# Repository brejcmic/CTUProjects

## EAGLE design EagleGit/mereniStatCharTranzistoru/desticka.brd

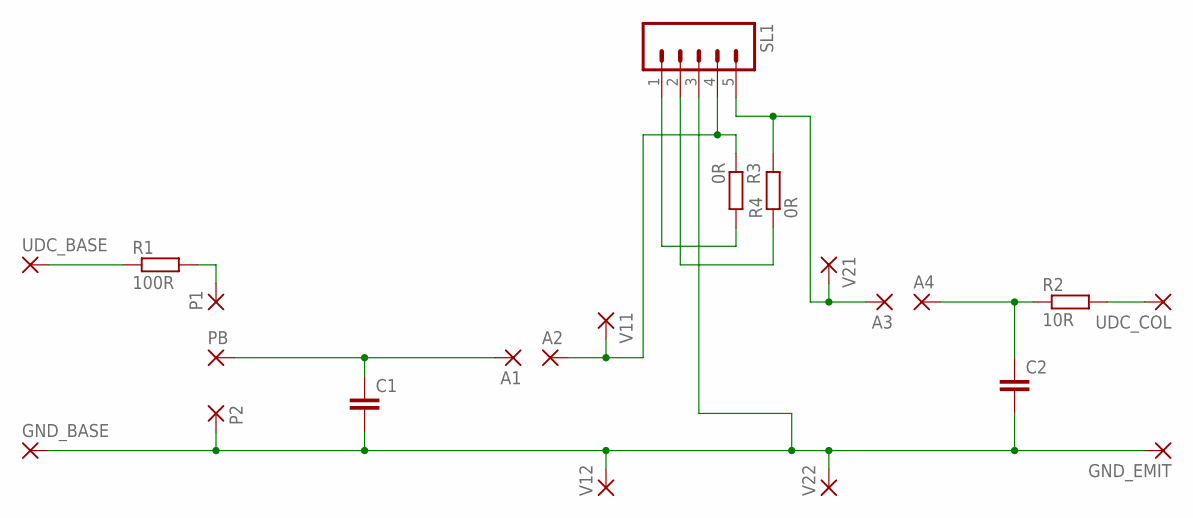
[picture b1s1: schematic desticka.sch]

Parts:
A1, A2, A3, A4: 3,17/1,3
C1, C2: C-EU050-055X075; C050-055X075
GND_BASE: 3,17/1,3
GND_EMIT: 3,17/1,3
P1, P2: 2,54/1,0
PB: 2,54/1,0
R1: 100R; P0613/15
R2: 10R; P0613/15
R3, R4: 0R; 0207/7
SL1: M05; 05P
UDC_BASE: 3,17/1,3
UDC_COL: 3,17/1,3
V11, V12, V21, V22: 3,17/1,3

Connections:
unnamed: A1.1, C1.1, PB.1
unnamed: R3.2, SL1.1
unnamed: R2.2, UDC_COL.1
unnamed: R1.1, UDC_BASE.1
unnamed: P1.1, R1.2
unnamed: R4.1, SL1.2
unnamed: A4.1, C2.1, R2.1
unnamed: C1.2, C2.2, GND_BASE.1, GND_EMIT.1, P2.1, SL1.3, V12.1, V22.1
unnamed: A3.1, R4.2, SL1.5, V21.1
unnamed: A2.1, R3.1, SL1.4, V11.1

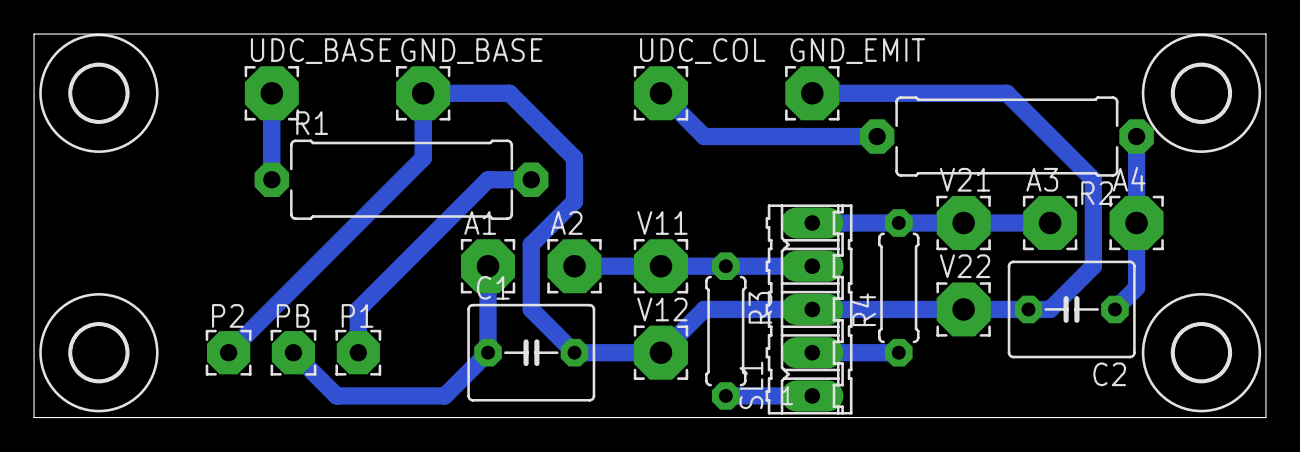
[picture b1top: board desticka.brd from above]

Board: 2 copper layers, 72.4 x 22.5 mm, 26 parts (0 on the bottom side), 10 nets.

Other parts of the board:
U$1, U$2, U$3, U$4: 3,2

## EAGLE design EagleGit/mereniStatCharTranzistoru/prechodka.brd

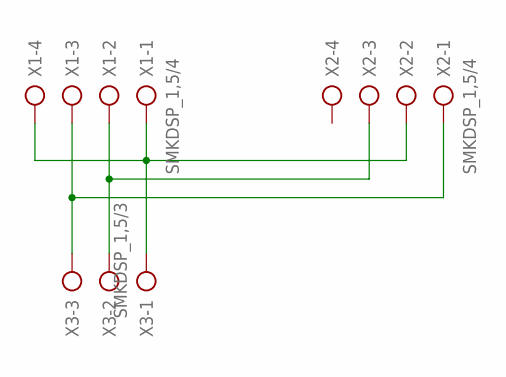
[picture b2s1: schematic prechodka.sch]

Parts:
X1, X2: SMKDSP_1,5/4
X3: SMKDSP_1,5/3

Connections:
BASE: X1.1, X1.4, X2.2, X3.1
COLECTOR: X1.2, X2.3, X3.2
EMITOR: X1.3, X2.1, X3.3

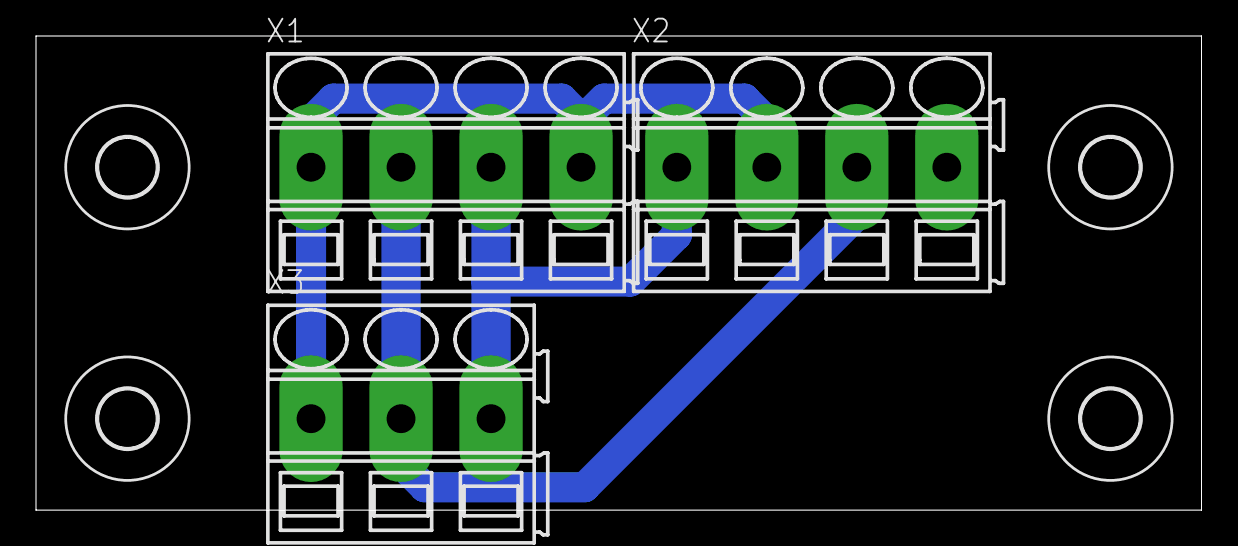
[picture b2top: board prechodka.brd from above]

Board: 2 copper layers, 64.8 x 26.3 mm, 7 parts (0 on the bottom side), 3 nets.

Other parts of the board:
U$1, U$2, U$3, U$4: 3,2

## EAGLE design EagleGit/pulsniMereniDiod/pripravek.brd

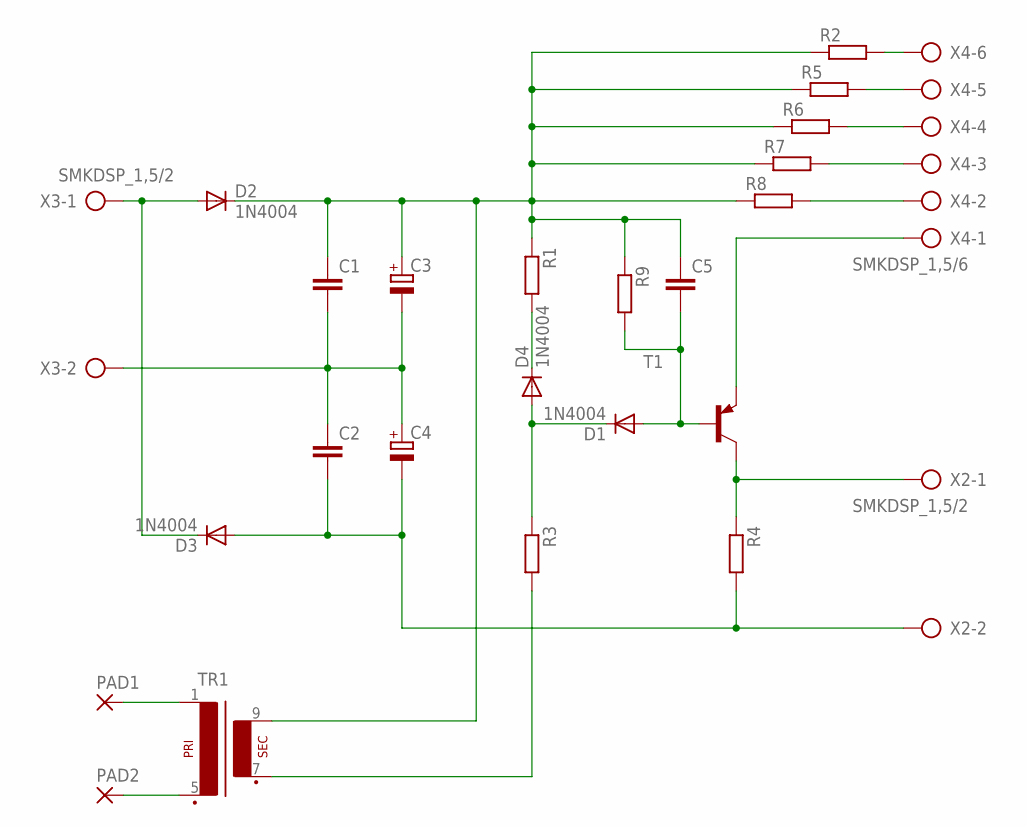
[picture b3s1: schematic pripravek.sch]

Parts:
C1, C2, C5: C-EU050-035X075; C050-035X075
C3, C4: CPOL-EUE5-8.5; E5-8,5
D1, D2, D3, D4: 1N4004; DO41-10
PAD1, PAD2: 3,81/1,3
R1, R3, R4, R9: R-EU_0207/12; 0207/12
R2, R5, R6, R7, R8: R-EU_0411/15; 0411/15
T1: -PNP-TO220V; TO220V
TR1: EI30-1
X2, X3: SMKDSP_1,5/2
X4: SMKDSP_1,5/6

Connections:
BASE: C5.2, D1.A, R9.2, T1.1 (B)
COLECTOR: R4.1, T1.2 (C), X2.1
EMITER: T1.3 (E), X4.1
unnamed: PAD1.1, TR1.1
unnamed: PAD2.1, TR1.5 (P2)
unnamed: R2.2, X4.6
unnamed: D1.C, D4.A, R3.1
unnamed: C1.2, C2.1, C3.-, C4.+, X3.2
unnamed: D4.C, R1.2
unnamed: D2.A, D3.C, X3.1
unnamed: C2.2, C4.-, D3.A, R4.2, X2.2
unnamed: R3.2, TR1.7 (S3)
unnamed: R5.2, X4.5
unnamed: C1.1, C3.+, C5.1, D2.C, R1.1, R2.1, R5.1, R6.1, R7.1, R8.1, R9.1, TR1.9 (S4)
unnamed: R6.2, X4.4
unnamed: R7.2, X4.3
unnamed: R8.2, X4.2

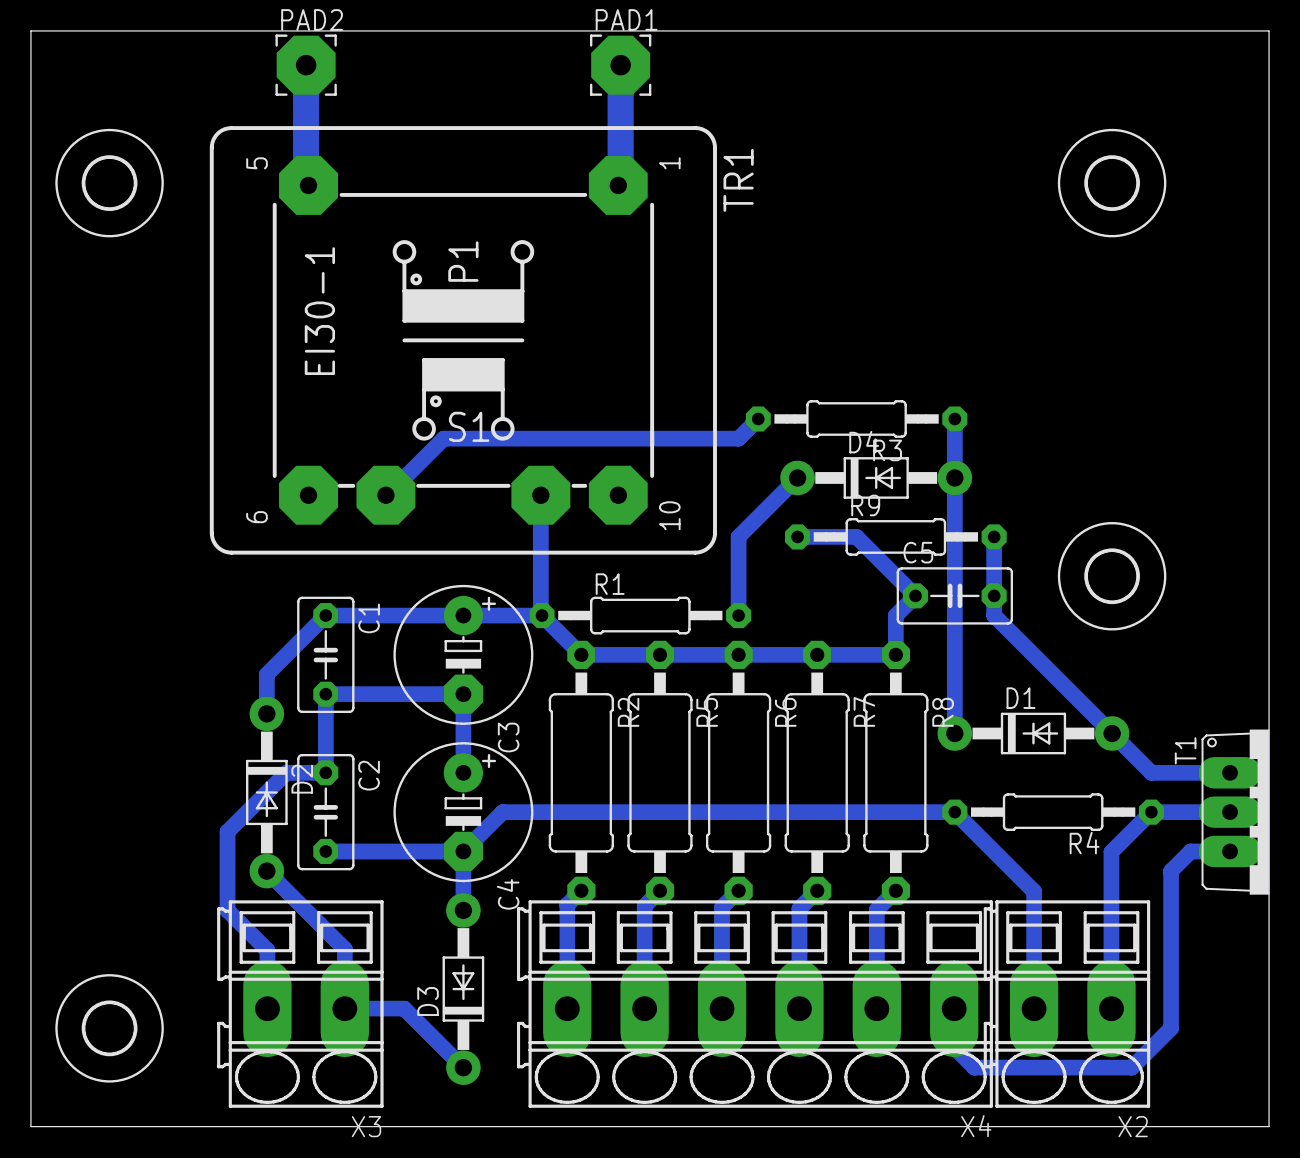
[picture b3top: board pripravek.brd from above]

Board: 2 copper layers, 80.0 x 70.8 mm, 29 parts (0 on the bottom side), 17 nets.

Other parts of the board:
U$1, U$2, U$3, U$4: 3,2

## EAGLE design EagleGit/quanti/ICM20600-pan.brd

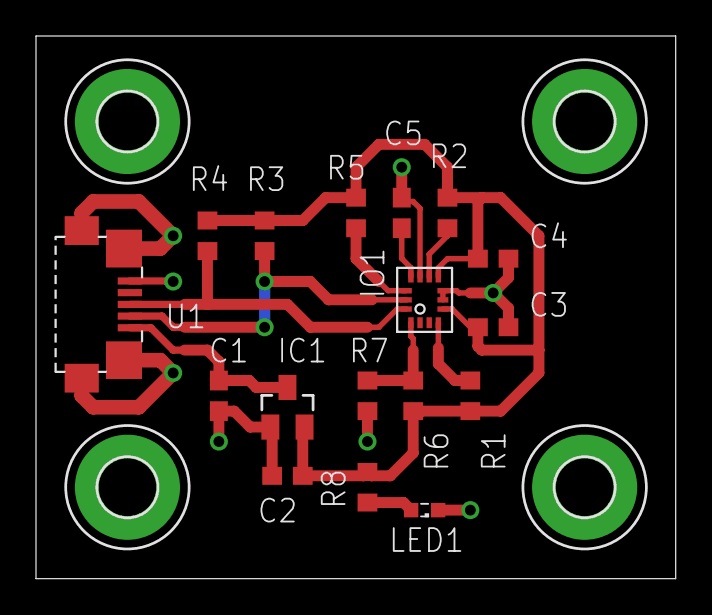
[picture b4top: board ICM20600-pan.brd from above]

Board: 2 copper layers, 35.5 x 30.1 mm, 21 parts (0 on the bottom side), 11 nets.

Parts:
C1, C2: 2u2; C0603
C3, C4, C5: 100n; C0603
H1, H2, H3, H4: MOUNT-PAD-ROUND3.2; 3,2-PAD
IC1: MCP1703CB; SOT23
IO1: LGA14
LED1: SML0603
R1, R2, R3, R4, R5, R6: 10k; R0603
R7: 0R; R0603
R8: 220R; R0603
U1: MICRO-USB-SHIELD-ZX62R-B-5P; ZX62R-B-5P

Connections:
+3V3: C2.1, C3.1, C4.1, IC1.2, IO1.P5, IO1.P8, R1.2, R2.2, R3.2, R4.2, R5.2, R6.2, R8.2
+5V: C1.1, IC1.3, U1.1
GND: C1.2, C2.2, C3.2, C4.2, C5.2, H1.B3,2, H2.B3,2, H3.B3,2, H4.B3,2, IC1.1, IO1.P6, IO1.P7, IO1.P10, LED1.C, R7.1, U1.5, U1.M1, U1.M2, U1.M3, U1.M4
unnamed: IO1.P9, R2.1
unnamed: IO1.P4, R1.1
unnamed: C5.1, IO1.P11
unnamed: IO1.P13, R3.1, U1.2
unnamed: IO1.P14, R4.1, U1.3
unnamed: IO1.P12, R5.1
unnamed: IO1.P1, R6.1, R7.2
unnamed: LED1.A, R8.1

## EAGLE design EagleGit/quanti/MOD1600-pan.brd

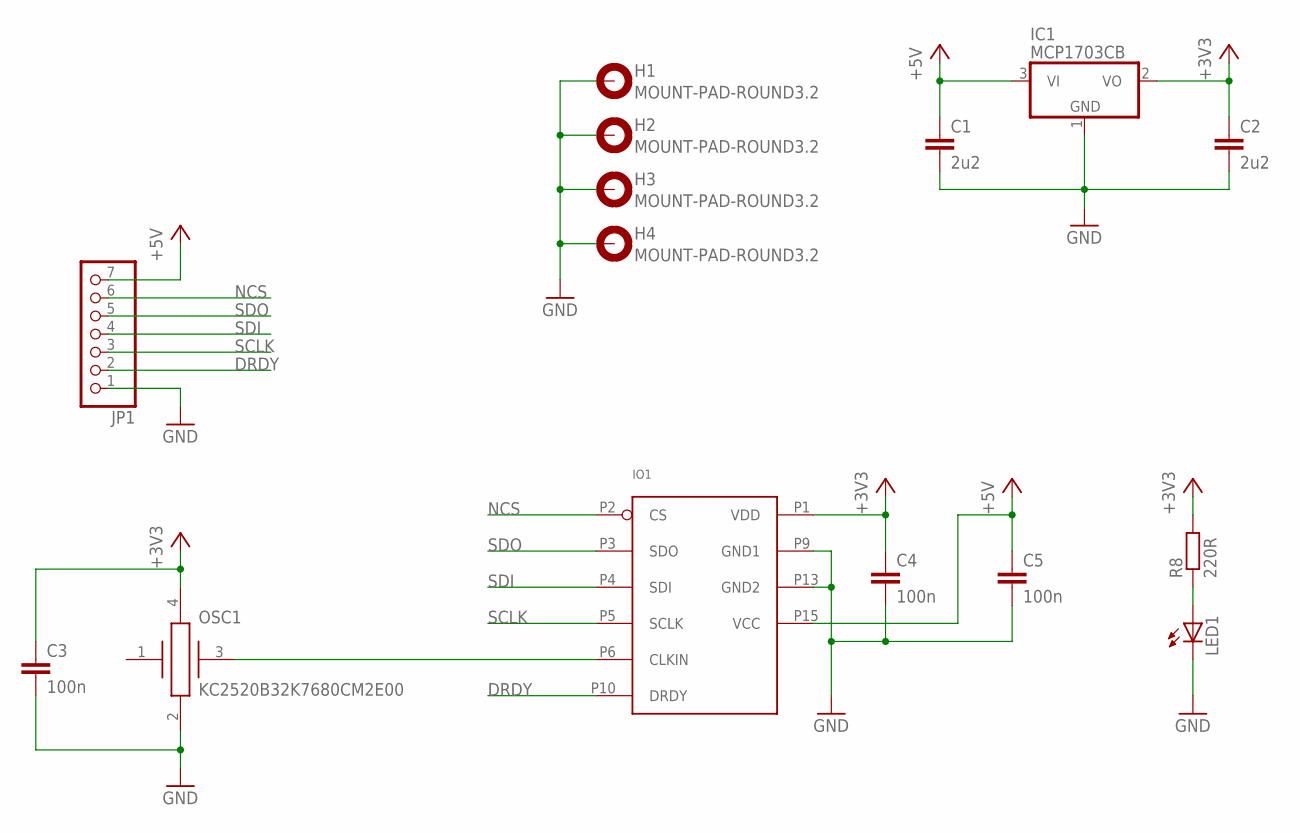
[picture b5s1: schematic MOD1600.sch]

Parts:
C1, C2: 2u2; C0603
C3, C4, C5: 100n; C0603
H1, H2, H3, H4: MOUNT-PAD-ROUND3.2; 3,2-PAD
IC1: MCP1703CB; SOT23
IO1: MOD1600; LGA_MOD1600
JP1: PINHD-1X7/90; 1X07/90
LED1: LEDSML0603; SML0603
OSC1: KC2520B32K7680CM2E00; SMD_OSC
R8: 220R; R0603

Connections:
+3V3: C2.1, C3.1, C4.1, IC1.2 (VO), IO1.P1 (VDD), OSC1.4 (VDD), R8.2
+5V: C1.1, C5.1, IC1.3 (VI), IO1.P15 (VCC), JP1.7
CLKIN: IO1.P6 (CLKIN), OSC1.3 (OUT)
DRDY: IO1.P10 (DRDY), JP1.2
GND: C1.2, C2.2, C3.2, C4.2, C5.2, H1.B3,2, H2.B3,2, H3.B3,2, H4.B3,2, IC1.1 (GND), IO1.P9 (GND1), IO1.P13 (GND2), JP1.1, LED1.C, OSC1.2 (GND)
unnamed: LED1.A, R8.1
NCS: IO1.P2 (CS), JP1.6
SCLK: IO1.P5 (SCLK), JP1.3
SDI: IO1.P4 (SDI), JP1.4
SDO: IO1.P3 (SDO), JP1.5

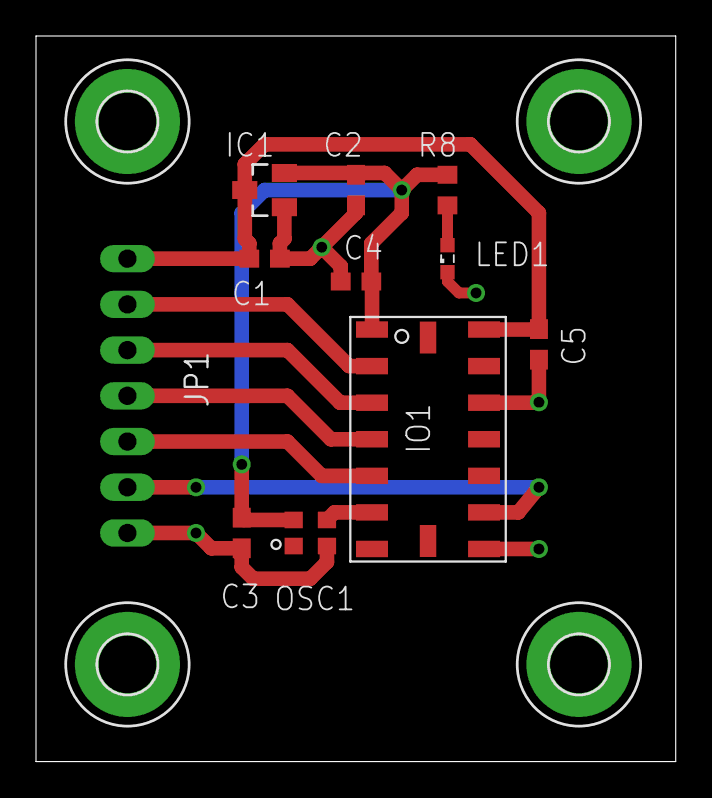
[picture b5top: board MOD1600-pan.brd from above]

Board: 2 copper layers, 35.5 x 40.3 mm, 15 parts (0 on the bottom side), 10 nets.

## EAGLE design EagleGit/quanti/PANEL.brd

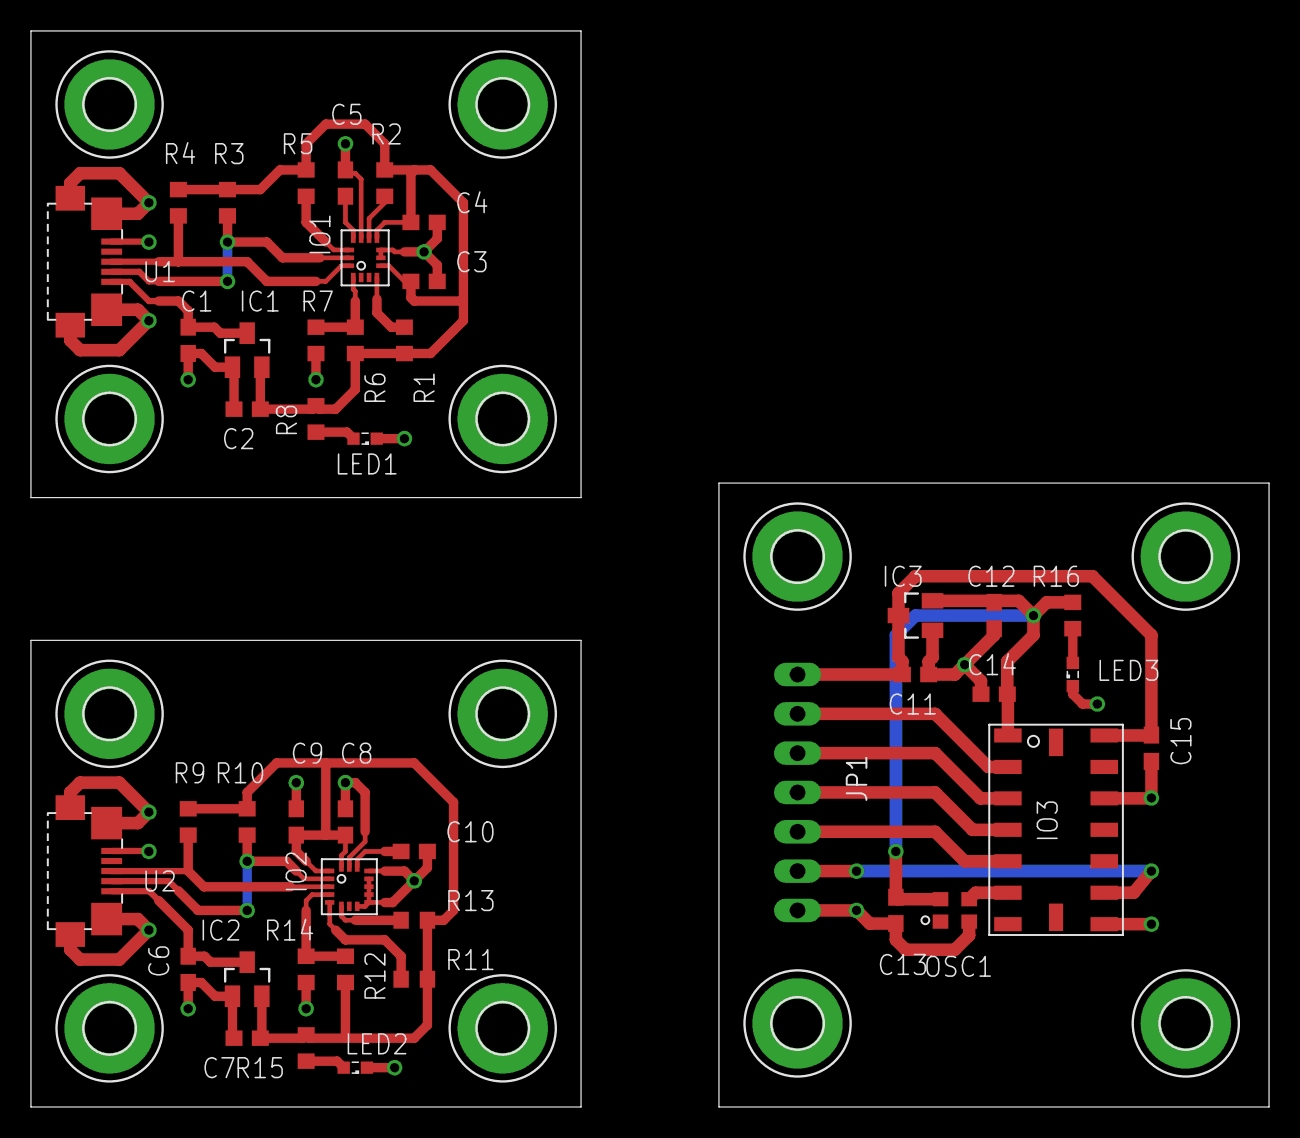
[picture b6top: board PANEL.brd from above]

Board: 2 copper layers, 80.0 x 69.5 mm, 56 parts (0 on the bottom side), 31 nets.

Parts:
C1, C2, C6, C7, C11, C12: 2u2; C0603
C3, C4, C5, C8, C9, C10, C13, C14, C15: 100n; C0603
H1, H2, H3, H4, H5, H6, H7, H8, H9, H10, H11, H12: MOUNT-PAD-ROUND3.2; 3,2-PAD
IC1, IC2, IC3: MCP1703CB; SOT23
IO1: LGA14
IO2: LGA16
IO3: LGA_MOD1600
JP1: 1X07/90
LED1, LED2, LED3: SML0603
OSC1: KC2520B32K7680CM2E00; SMD_OSC
R1, R2, R3, R4, R5, R6, R9, R10, R11, R12, R13: 10k; R0603
R7, R14: 0R; R0603
R8, R15, R16: 220R; R0603
U1: MICRO-USB-SHIELD-ZX62R-B-5P; ZX62R-B-5P
U2: MICRO-USB; ZX62R-B-5P

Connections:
+3V1: C7.1, C8.1, C9.1, IC2.2, IO2.P1, IO2.P16, R9.2, R10.2, R11.2, R12.2, R13.2, R15.2
+3V2: C12.1, C13.1, C14.1, IC3.2, IO3.P1, OSC1.4, R16.2
+3V3: C2.1, C3.1, C4.1, IC1.2, IO1.P5, IO1.P8, R1.2, R2.2, R3.2, R4.2, R5.2, R6.2, R8.2
+5V: C1.1, IC1.3, U1.1
+5V1: C6.1, IC2.3, U2.1
+5V2: C11.1, C15.1, IC3.3, IO3.P15, JP1.7
CLKIN: IO3.P6, OSC1.3
DRDY: IO3.P10, JP1.2
GND: C1.2, C2.2, C3.2, C4.2, C5.2, H1.B3,2, H2.B3,2, H3.B3,2, H4.B3,2, IC1.1, IO1.P6, IO1.P7, IO1.P10, LED1.C, R7.1, U1.5, U1.M1, U1.M2, U1.M3, U1.M4
GND1: C6.2, C7.2, C8.2, C9.2, C10.2, H5.B3,2, H6.B3,2, H7.B3,2, H8.B3,2, IC2.1, IO2.P8, IO2.P9, IO2.P10, IO2.P11, IO2.P12, IO2.P13, IO2.P15, LED2.C, R14.1, U2.5, U2.M1, U2.M2, U2.M3, U2.M4
GND2: C11.2, C12.2, C13.2, C14.2, C15.2, H9.B3,2, H10.B3,2, H11.B3,2, H12.B3,2, IC3.1, IO3.P9, IO3.P13, JP1.1, LED3.C, OSC1.2
unnamed: IO1.P9, R2.1
unnamed: IO1.P4, R1.1
unnamed: C5.1, IO1.P11
unnamed: IO1.P13, R3.1, U1.2
unnamed: IO1.P14, R4.1, U1.3
unnamed: LED2.A, R15.1
unnamed: IO1.P12, R5.1
unnamed: IO1.P1, R6.1, R7.2
unnamed: LED1.A, R8.1
unnamed: C10.1, IO2.P14
unnamed: IO2.P2, R10.1, U2.2
unnamed: IO2.P3, R9.1, U2.3
unnamed: IO2.P5, R11.1
unnamed: IO2.P4, R12.1, R14.2
unnamed: IO2.P6, R13.1
unnamed: LED3.A, R16.1
NCS: IO3.P2, JP1.6
SCLK: IO3.P5, JP1.3
SDI: IO3.P4, JP1.4
SDO: IO3.P3, JP1.5
